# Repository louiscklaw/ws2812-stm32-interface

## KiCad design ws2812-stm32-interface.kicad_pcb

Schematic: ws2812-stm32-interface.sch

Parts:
C1, C2, C3, C4, C5: 10u; C_0805_2012Metric_Pad1.15x1.40mm_HandSolder
J1: Conn_01x03; PinHeader_1x03_P2.54mm_Vertical
J2: Conn_01x03; mstbva_2,5-4-g-5,08
J3: WS2812_DEST; PinHeader_1x04_P2.54mm_Vertical
J4: WS2812_SOURCE; PinHeader_1x04_P2.54mm_Vertical
JP1: Jumper_NC_Dual; PinHeader_1x03_P2.54mm_Vertical
LD_G1: GREEN; LED_0805_2012Metric_Pad1.15x1.40mm_HandSolder
LD_O1: ORANGE; LED_0805_2012Metric_Pad1.15x1.40mm_HandSolder
R1, R2: 104; R_0805_2012Metric_Pad1.15x1.40mm_HandSolder
U1: 74AHCT1G125; SOT-23-5_HandSoldering
ZD1, ZD2: MBR120; D_SOD-123F

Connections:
+5V: J1.2, R1.1, ZD1.2
/MCU_LED_PWM: J1.3, U1.2
/PWM_TO_LED: J2.3, JP1.3, U1.4
/led_array/WS2812_DIN: JP1.2; also elsewhere on the board
/led_array/WS2812_DOUT: J3.3; also elsewhere on the board
GND: C1.2, C2.2, C3.2, C4.2, C5.2, J1.1, J2.4, J3.4, J4.4, LD_G1.1, LD_O1.1, U1.1, U1.3 (GND); also elsewhere on the board
unnamed: J4.3, JP1.1
unnamed: LD_G1.2, R1.2
unnamed: LD_O1.2, R2.2
VCC: C1.1, C2.1, C3.1, C4.1, C5.1, J2.2, J3.2, J4.2, R2.1, U1.5 (VCC), ZD1.1, ZD2.1; also elsewhere on the board
V_EXT_LED: J2.1, J3.1, J4.1, ZD2.2

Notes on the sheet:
LEGEND: +5V: 5V supply from MCU side, V_EXT_LED: 5V power supply from LED strap(if possible) VDD: joined power supply to LED strap

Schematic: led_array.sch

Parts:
D1, D2, D3, D4, D5, D6, D7, D8, D9, D10, D11, D12, D13, D14, D15, D16, D17, D18, D19, D20, D21, D22, D23, D24, D25, D26, D27, D28, D29, D30, D31, D32, D33, D34, D35, D36, D37, D38, D39, D40, D41, D42, D43, D44, D45, D46, D47, D48, D49, D50, D51, D52, D53, D54, D55, D56, D57, D58, D59, D60, D61, D62, D63, D64: WS2812B; LED_WS2812B_PLCC4_5.0x5.0mm_P3.2mm

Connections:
/led_array/WS2812_DIN: D1.4; also elsewhere on the board
/led_array/WS2812_DOUT: D64.2; also elsewhere on the board
GND: D1.3, D2.3, D3.3, D4.3, D5.3, D6.3, D7.3, D8.3, D9.3, D10.3, D11.3, D12.3, D13.3, D14.3, D15.3, D16.3, D17.3, D18.3, D19.3, D20.3, D21.3, D22.3, D23.3, D24.3, D25.3, D26.3, D27.3, D28.3, D29.3, D30.3, D31.3, D32.3, D33.3, D34.3, D35.3, D36.3, D37.3, D38.3, D39.3, D40.3, D41.3, D42.3, D43.3, D44.3, D45.3, D46.3, D47.3, D48.3, D49.3, D50.3, D51.3, D52.3, D53.3, D54.3, D55.3, D56.3, D57.3, D58.3, D59.3, D60.3, D61.3, D62.3, D63.3, D64.3; also elsewhere on the board
unnamed: D1.2, D2.4
unnamed: D2.2, D3.4
unnamed: D3.2, D4.4
unnamed: D4.2, D5.4
unnamed: D5.2, D6.4
unnamed: D6.2, D7.4
unnamed: D7.2, D8.4
unnamed: D8.2, D9.4
unnamed: D10.2, D11.4
unnamed: D9.2, D10.4
unnamed: D11.2, D12.4
unnamed: D12.2, D13.4
unnamed: D13.2, D14.4
unnamed: D14.2, D15.4
unnamed: D15.2, D16.4
unnamed: D16.2, D17.4
unnamed: D17.2, D18.4
unnamed: D18.2, D19.4
unnamed: D19.2, D20.4
unnamed: D20.2, D21.4
unnamed: D21.2, D22.4
unnamed: D22.2, D23.4
unnamed: D23.2, D24.4
unnamed: D24.2, D25.4
unnamed: D25.2, D26.4
unnamed: D26.2, D27.4
unnamed: D27.2, D28.4
unnamed: D28.2, D29.4
unnamed: D29.2, D30.4
unnamed: D30.2, D31.4
unnamed: D31.2, D32.4
unnamed: D32.2, D33.4
unnamed: D33.2, D34.4
unnamed: D34.2, D35.4
unnamed: D35.2, D36.4
unnamed: D36.2, D37.4
unnamed: D37.2, D38.4
unnamed: D38.2, D39.4
unnamed: D39.2, D40.4
unnamed: D40.2, D41.4
unnamed: D41.2, D42.4
unnamed: D42.2, D43.4
unnamed: D43.2, D44.4
unnamed: D44.2, D45.4
unnamed: D45.2, D46.4
unnamed: D46.2, D47.4
unnamed: D47.2, D48.4
unnamed: D48.2, D49.4
unnamed: D49.2, D50.4
unnamed: D50.2, D51.4
unnamed: D51.2, D52.4
unnamed: D52.2, D53.4
unnamed: D53.2, D54.4
unnamed: D54.2, D55.4
unnamed: D55.2, D56.4
unnamed: D56.2, D57.4
unnamed: D57.2, D58.4
unnamed: D58.2, D59.4
unnamed: D59.2, D60.4
unnamed: D60.2, D61.4
unnamed: D61.2, D62.4
unnamed: D62.2, D63.4
unnamed: D63.2, D64.4
VCC: D1.1, D2.1, D3.1, D4.1, D5.1, D6.1, D7.1, D8.1, D9.1, D10.1, D11.1, D12.1, D13.1, D14.1, D15.1, D16.1, D17.1, D18.1, D19.1, D20.1, D21.1, D22.1, D23.1, D24.1, D25.1, D26.1, D27.1, D28.1, D29.1, D30.1, D31.1, D32.1, D33.1, D34.1, D35.1, D36.1, D37.1, D38.1, D39.1, D40.1, D41.1, D42.1, D43.1, D44.1, D45.1, D46.1, D47.1, D48.1, D49.1, D50.1, D51.1, D52.1, D53.1, D54.1, D55.1, D56.1, D57.1, D58.1, D59.1, D60.1, D61.1, D62.1, D63.1, D64.1; also elsewhere on the board

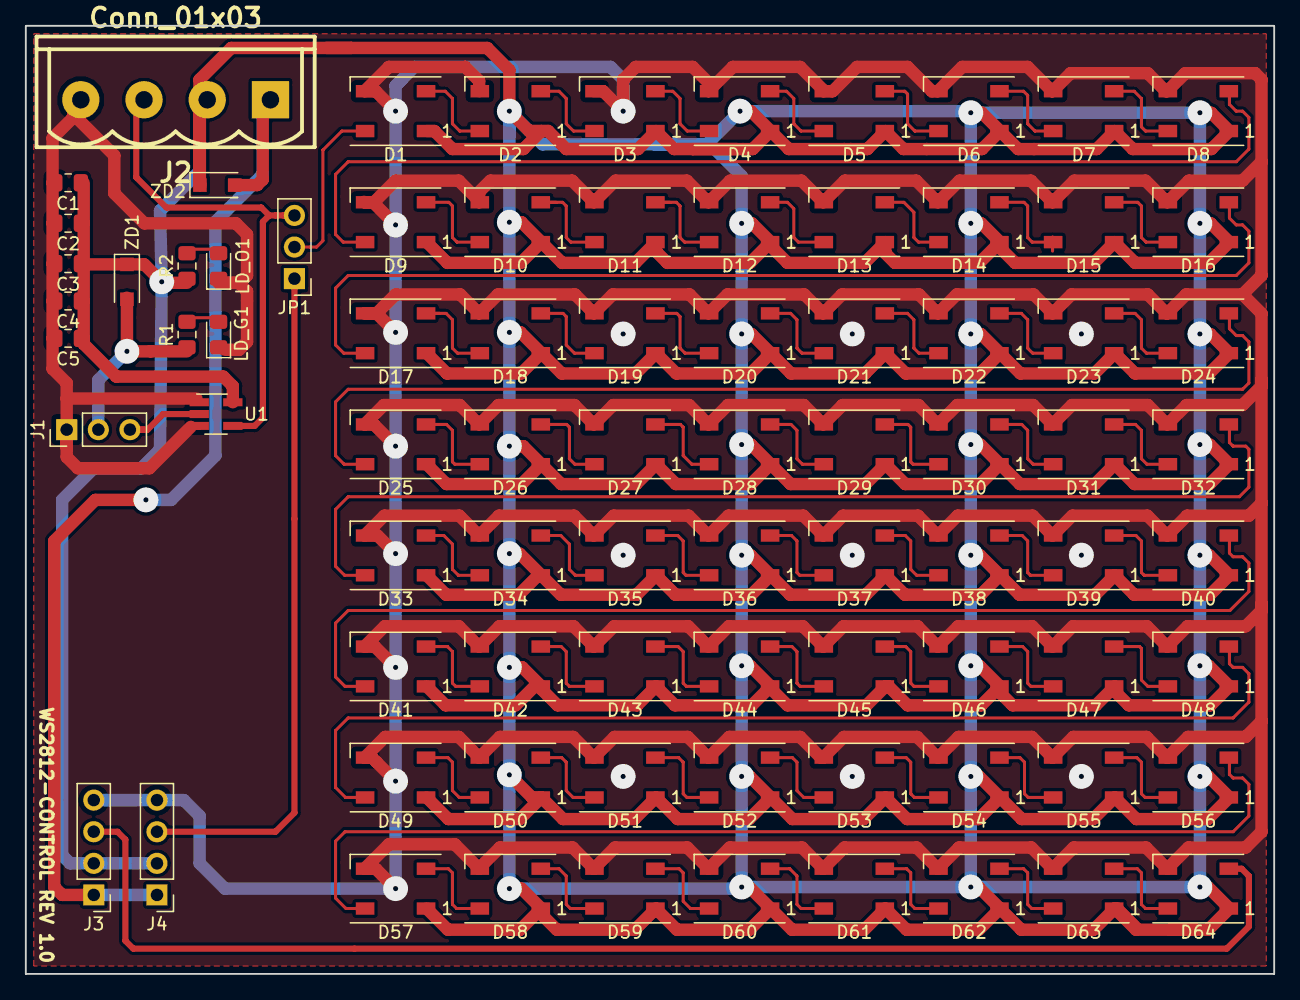
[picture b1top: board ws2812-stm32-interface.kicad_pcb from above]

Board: 2 copper layers, 100.3 x 76.2 mm, 81 parts (0 on the bottom side), 74 nets.

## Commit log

2018-10-07 init commit,
2018-10-07 update,
2020-05-07 ci: init travis build config,
2020-05-07 ci: init travis token,
